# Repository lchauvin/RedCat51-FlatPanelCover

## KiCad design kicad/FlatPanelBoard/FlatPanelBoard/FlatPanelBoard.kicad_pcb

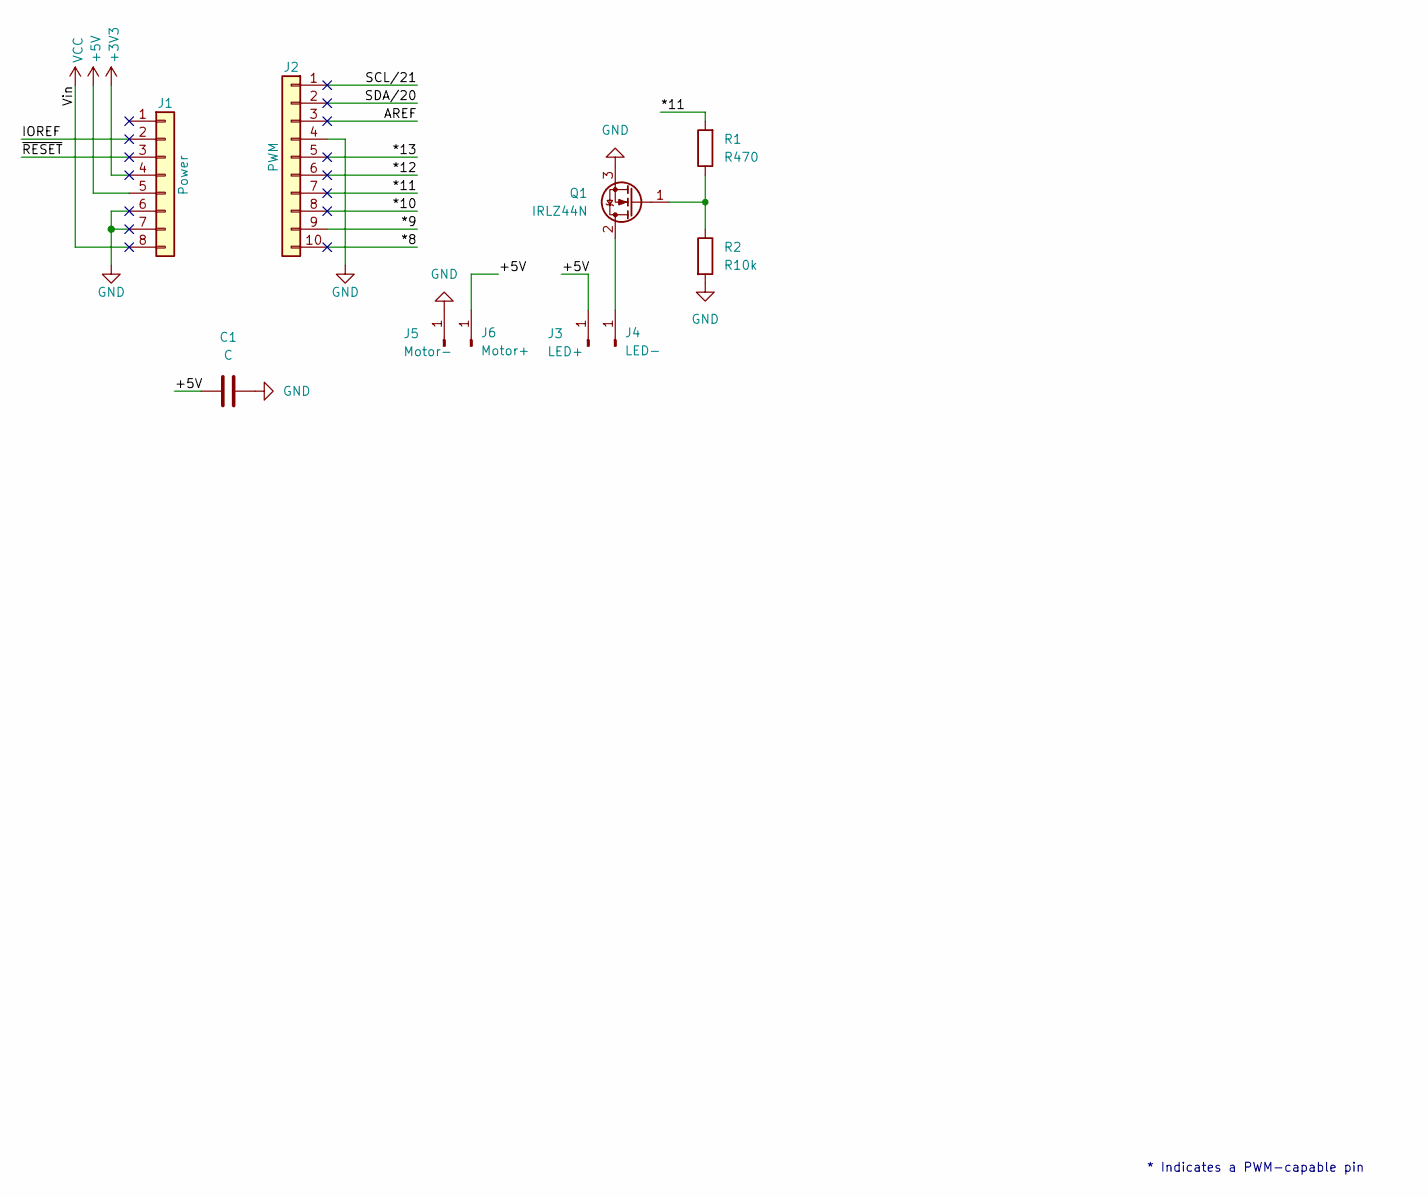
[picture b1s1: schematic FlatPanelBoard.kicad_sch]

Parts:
C1: C; CP_Radial_D8.0mm_P3.50mm
J1: Power; PinSocket_1x08_P2.54mm_Vertical
J2: PWM; PinSocket_1x10_P2.54mm_Vertical
J3: LED+; Pin_D1.0mm_L10.0mm
J4: LED-; Pin_D1.0mm_L10.0mm
J5: Motor-; Pin_D1.0mm_L10.0mm
J6: Motor+; Pin_D1.0mm_L10.0mm
Q1: IRLZ44N; TO-220-3_Vertical
R1: R470; R_Axial_DIN0207_L6.3mm_D2.5mm_P10.16mm_Horizontal
R2: R10k; R_Axial_DIN0207_L6.3mm_D2.5mm_P10.16mm_Horizontal

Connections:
+3V3: J1.4
+5V: C1.1, J1.5, J3.1 (Pin_1_1), J6.1 (Pin_1_1)
/*8: J2.10
/*9: J2.9
/*10: J2.8
/*11: J2.7, R1.2
/*12: J2.6
/*13: J2.5
/AREF: J2.3
/IOREF: J1.2
/SCL/21: J2.1
/SDA/20: J2.2
/~RESET: J1.3
GND: C1.2, J1.6, J1.7, J2.4, J5.1 (Pin_1_1), Q1.3 (S), R2.2
unnamed: J4.1 (Pin_1_1), Q1.2 (D)
unnamed: Q1.1 (G), R1.1, R2.1
VCC: J1.8

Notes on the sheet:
* Indicates a PWM-capable pin

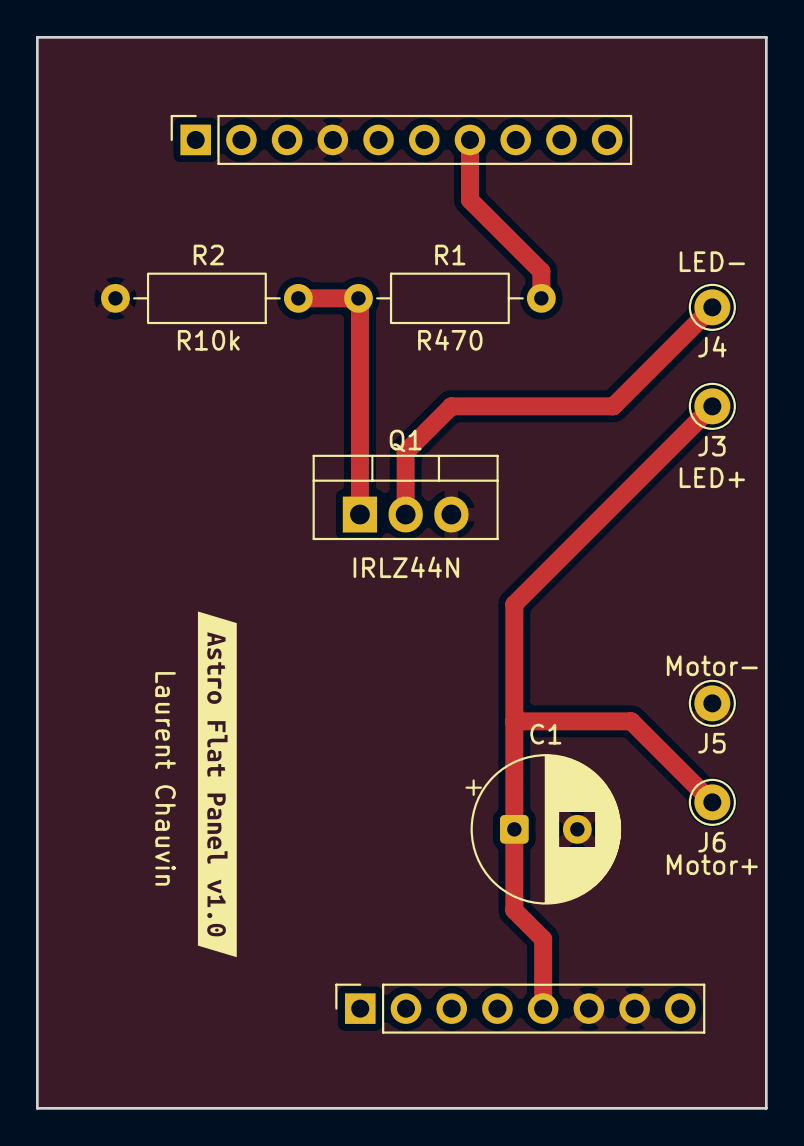
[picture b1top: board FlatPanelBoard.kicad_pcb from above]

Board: 2 copper layers, 40.5 x 59.5 mm, 11 parts (0 on the bottom side), 5 nets.

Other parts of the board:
kibuzzard-6A5A3A85: G***; kibuzzard-6A5A3A85

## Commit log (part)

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2026-04-17 Changed for pin 11 on Arduino to allow for finer control of the dimming
2026-04-19 Less brightness but more finesse
